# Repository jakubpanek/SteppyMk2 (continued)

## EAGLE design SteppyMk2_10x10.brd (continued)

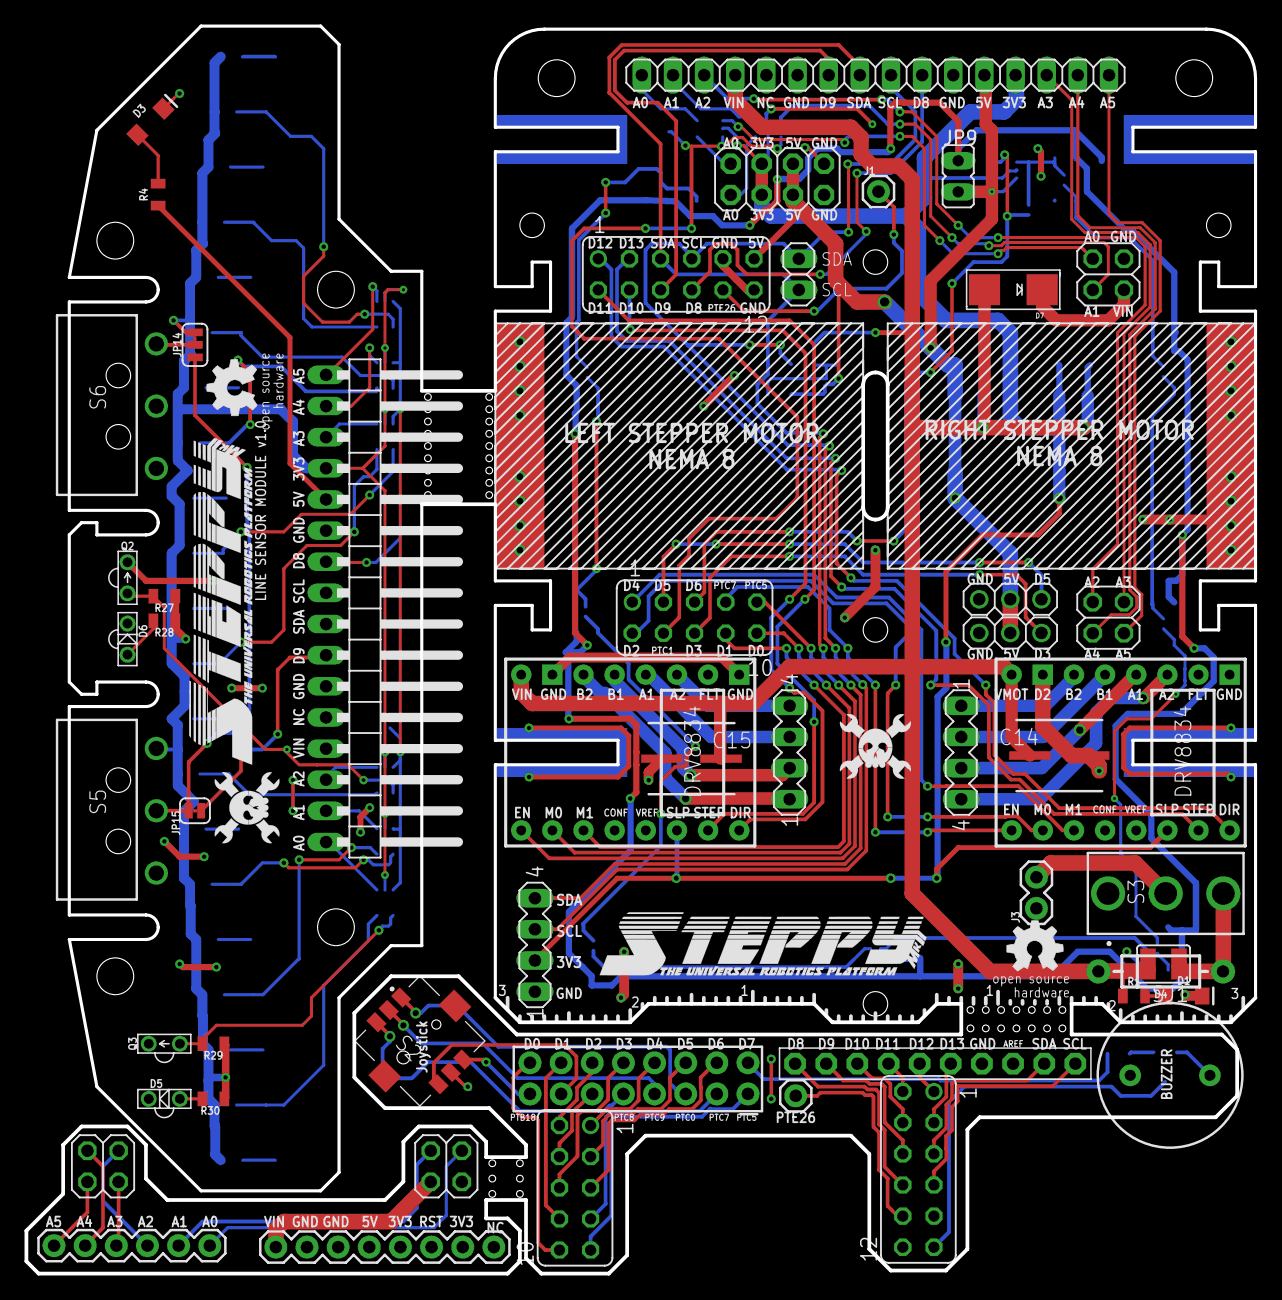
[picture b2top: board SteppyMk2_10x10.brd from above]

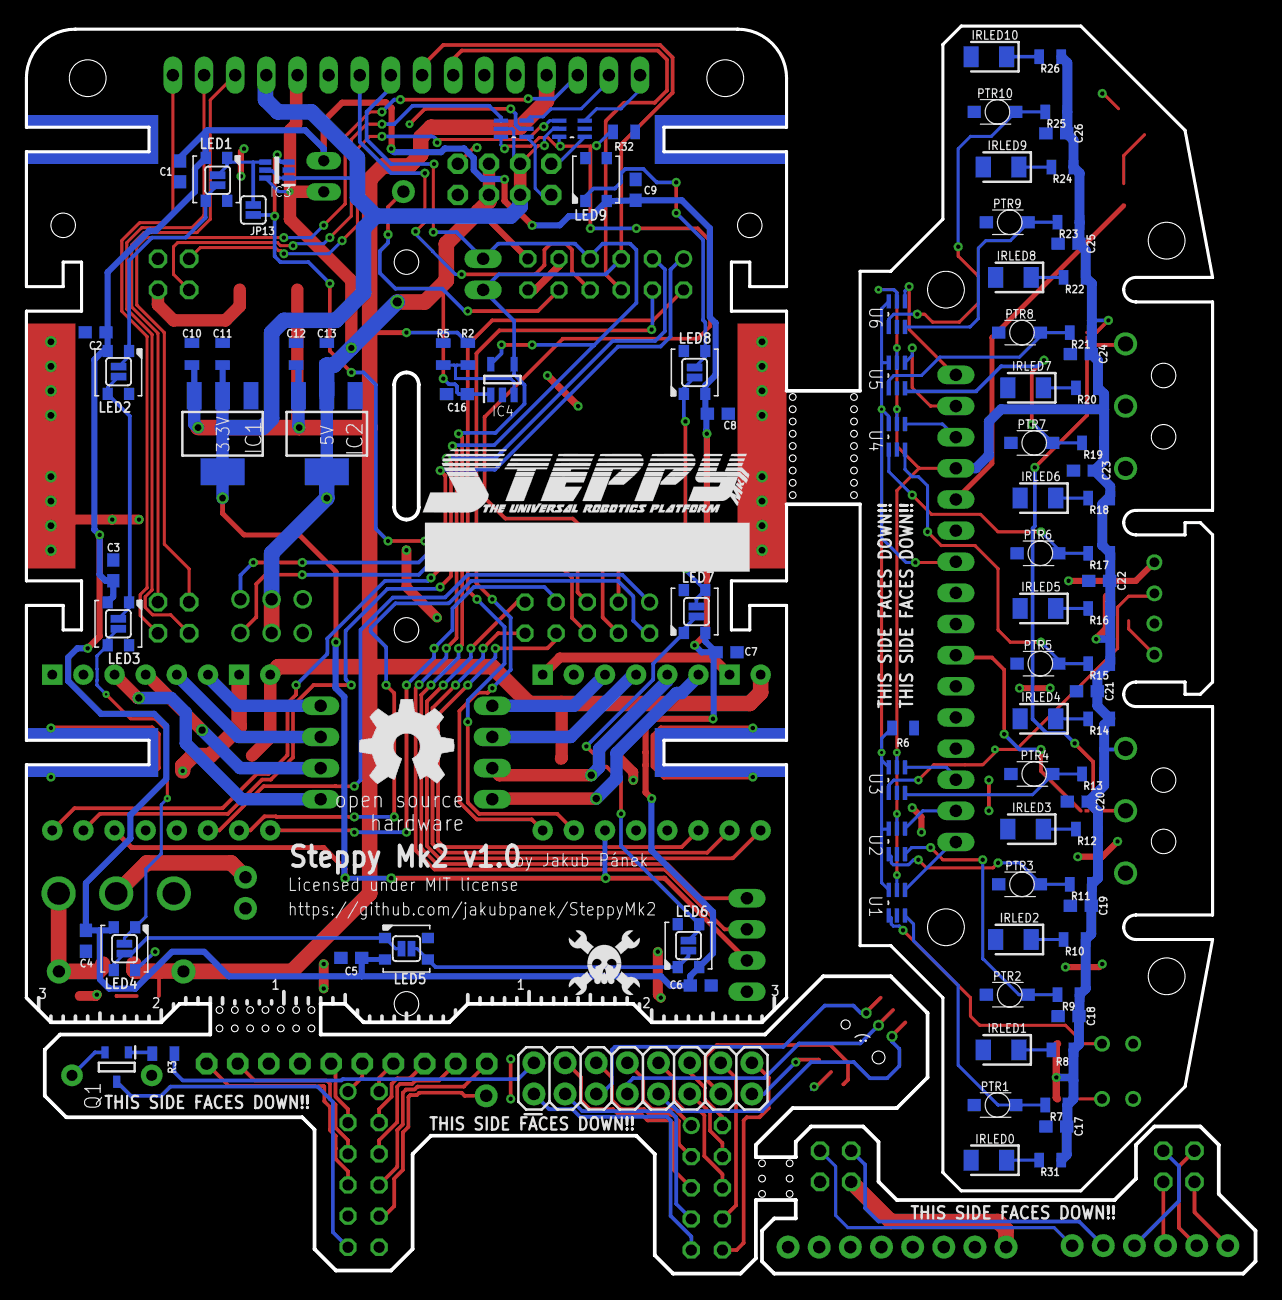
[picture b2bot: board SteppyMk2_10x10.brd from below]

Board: 2 copper layers, 100.2 x 101.8 mm, 156 parts (104 on the bottom side), 129 nets.

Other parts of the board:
GOLD_ORB_SM3: OSHWLOGOLOGO5MM; OSHW_5MM

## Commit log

2019-03-24 Update LICENSE
2019-04-14 V1.0 Eagle files
2019-04-14 Rename SteppyMk2.brd to Eagle Files/V1.0/SteppyMk2.brd
2019-04-14 Rename SteppyMk2.sch to Eagle Files/V1.0/SteppyMk2.sch
2019-04-14 Rename SteppyMk2_10x10.brd to Eagle Files/V1.0/SteppyMk2_10x10.brd
2019-04-14 Rename SteppyMk2_10x10.sch to Eagle Files/V1.0/SteppyMk2_10x10.sch
2019-04-14 Created folder "Graphics"
2019-04-14 Gerbers
2019-04-14 Added model of SMD joystick cap
2019-05-09 Added motor holder models
2019-08-08 Added files
